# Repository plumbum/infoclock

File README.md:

HMI WiFi board
==============

Features
--------

  * STM32F103Cxxx MCU;
  * TFT LCD 3.2" with resistive touchscreen;
  * WiFi ESP8266 based module;
  * USB device;
  * MicroSD card slot;
  * Buzzer;
  * DHT22 themperature/humidity sensor.

Library
-------

  * [ChibiOS/RT](http://www.chibios.org/)
  * [uGFX](http://ugfx.org/)

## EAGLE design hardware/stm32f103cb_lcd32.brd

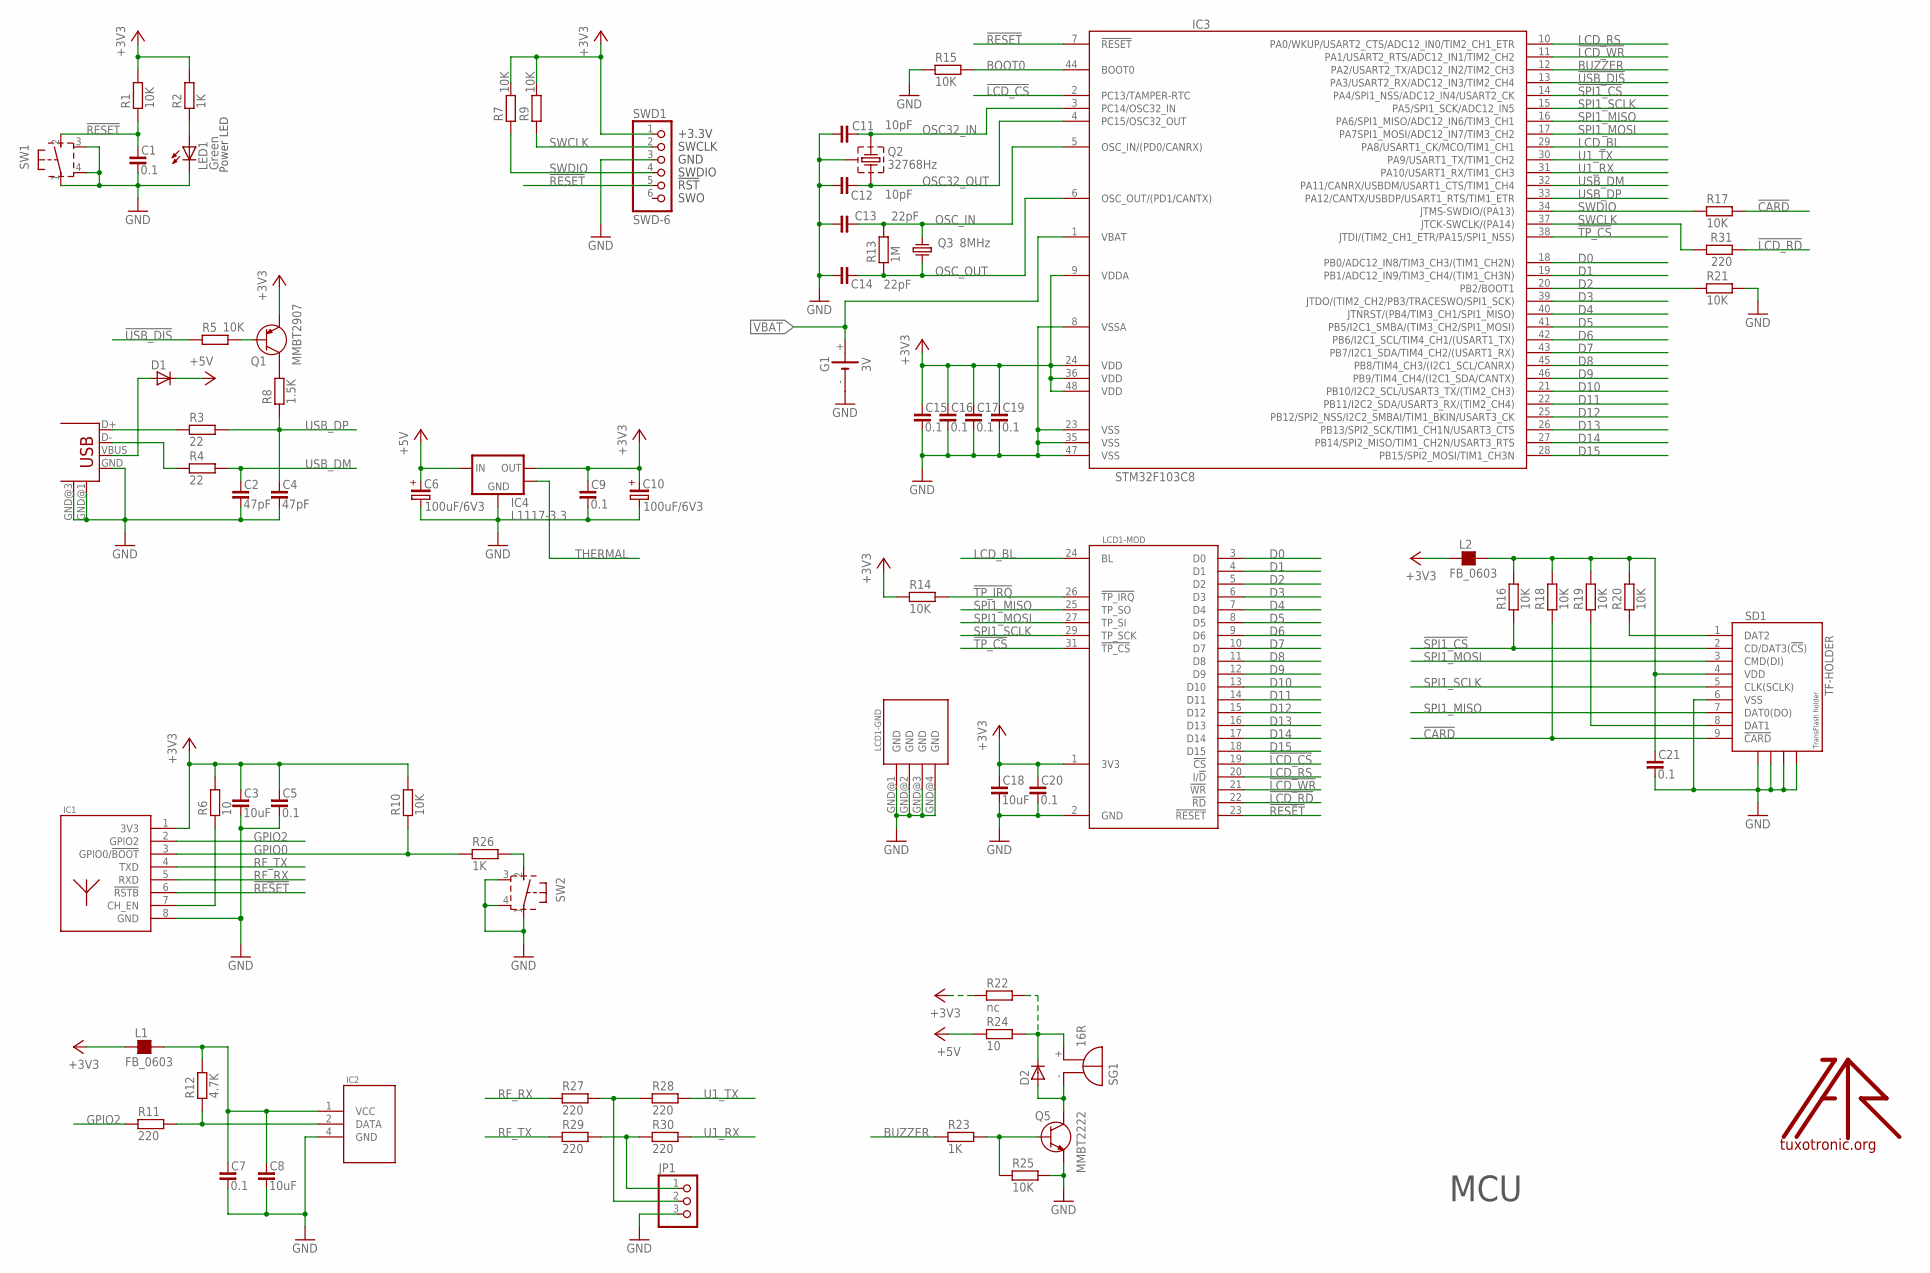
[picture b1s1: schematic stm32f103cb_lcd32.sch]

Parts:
C1, C5, C7, C15, C16, C17, C19, C20, C21: 0.1; C0603
C2, C4: 47pF; C0603
C3, C8, C18: 10uF; C0805
C6, C10: 100uF/6V3; SMC_D
C9: 0.1; C0805
C11, C12: 10pF; C0603
C13, C14: 22pF; C0603
D1: D-SMB; SMB
D2: D-SOD-80; SOD80
G1: 3V; SMT1220
IC1: ESP-11; ESP11
IC2: DHT22; DHT
IC3: STM32F103C8; LQFP48
IC4: L1117-3.3; SOT223-THP
JP1: PINHD-1X3_2.54S; 1X03SMALL
L1, L2: FB_0603; L0603
LCD1: YX32B
LED1: Green; CHIP-LED0805
LOGO1: LOGO; TT_LOGO
Q1: MMBT2907; SOT23
Q2: 32768Hz; TC38H-G
Q3: 8MHz; HC49/S
Q5: MMBT2222; SOT23
R1, R5, R7, R9, R10, R14, R15, R16, R17, R18, R19, R20, R21, R25: 10K; R0603
R2, R23, R26: 1K; R0603
R3, R4: 22; R0603
R6, R24: 10; R0603
R8: 1.5K; R0603
R11, R27, R28, R29, R30, R31: 220; R0603
R12: 4.7K; R0603
R13: 1M; R0603
R22: nc; R0603
SD1: TF-HOLDER; TF-PULL
SG1: 16R; F/QMBIII
SW1, SW2: 31-XX; B3F-31XX
SWD1: SWD-6; JTAG6PIN
USB1: USB-MB-S

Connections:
!CARD: R17.2, R18.1, SD1.9 (!CARD)
!LCD_CS: IC3.2 (PC13/TAMPER-RTC), LCD1.19 (!CS)
!LCD_RD: LCD1.22 (!RD), R31.1
!LCD_WR: IC3.11 (PA1/USART2_RTS/ADC12_IN1/TIM2_CH2), LCD1.21 (!WR)
!RESET: C1.1, IC1.6 (!RSTB), IC3.7 (!RESET), LCD1.23 (!RESET), R1.1, SW1.2 (S), SWD1.5
!SPI1_CS: IC3.14 (PA4/SPI1_NSS/ADC12_IN4/USART2_CK), R16.1, SD1.2 (CD/DAT3(!CS!))
!TP_CS: IC3.38 (JTDI/(TIM2_CH1_ETR/PA15/SPI1_NSS)), LCD1.31 (!TP_CS)
!TP_IRQ: LCD1.26 (!TP_IRQ), R14.2
!USB_DIS: IC3.13 (PA3/USART2_RX/ADC12_IN3/TIM2_CH4), R5.1
+3V3: C3.1, C5.1, C9.1, C10.+, C15.1, C16.1, C17.1, C18.1, C19.1, C20.1, IC1.1 (3V3), IC3.9 (VDDA), IC3.24 (VDD), IC3.36 (VDD), IC3.48 (VDD), IC4.2 (OUT), L1.1, L2.1, LCD1.1 (3V3), Q1.2 (E), R1.2, R2.2, R6.2, R7.2, R9.2, R10.2, R14.1, R22.1, SWD1.1
+5V: C6.+, D1.1 (C), IC4.3 (IN), R24.1
BOOT0: IC3.44 (BOOT0), R15.2
BUZZER: IC3.12 (PA2/USART2_TX/ADC12_IN2/TIM2_CH3), R23.1
D0: IC3.18 (PB0/ADC12_IN8/TIM3_CH3/(TIM1_CH2N)), LCD1.3 (D0)
D1: IC3.19 (PB1/ADC12_IN9/TIM3_CH4/(TIM1_CH3N)), LCD1.4 (D1)
D2: IC3.20 (PB2/BOOT1), LCD1.5 (D2), R21.1
D3: IC3.39 (JTDO/(TIM2_CH2/PB3/TRACESWO/SPI1_SCK)), LCD1.6 (D3)
D4: IC3.40 (JTNRST/(PB4/TIM3_CH1/SPI1_MISO)), LCD1.7 (D4)
D5: IC3.41 (PB5/I2C1_SMBA/(TIM3_CH2/SPI1_MOSI)), LCD1.8 (D5)
D6: IC3.42 (PB6/I2C1_SCL/TIM4_CH1/(USART1_TX)), LCD1.9 (D6)
D7: IC3.43 (PB7/I2C1_SDA/TIM4_CH2/(USART1_RX)), LCD1.10 (D7)
D8: IC3.45 (PB8/TIM4_CH3/(I2C1_SCL/CANRX)), LCD1.11 (D8)
D9: IC3.46 (PB9/TIM4_CH4/(I2C1_SDA/CANTX)), LCD1.12 (D9)
D10: IC3.21 (PB10/I2C2_SCL/USART3_TX/(TIM2_CH3)), LCD1.13 (D10)
D11: IC3.22 (PB11/I2C2_SDA/USART3_RX/(TIM2_CH4)), LCD1.14 (D11)
D12: IC3.25 (PB12/SPI2_NSS/I2C2_SMBAI/TIM1_BKIN/USAR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), LCD1.15 (D12)
D13: IC3.26 (PB13/SPI2_SCK/TIM1_CH1N/USART3_CTS), LCD1.16 (D13)
D14: IC3.27 (PB14/SPI2_MISO/TIM1_CH2N/USART3_RTS), LCD1.17 (D14)
D15: IC3.28 (PB15/SPI2_MOSI/TIM1_CH3N), LCD1.18 (D15)
GND: C1.2, C2.2, C3.2, C4.2, C5.2, C6.-, C7.2, C8.2, C9.2, C10.-, C11.2, C12.2, C13.2, C14.2, C15.2, C16.2, C17.2, C18.2, C19.2, C20.2, C21.2, G1.-, IC1.8 (GND), IC2.4 (GND), IC3.8 (VSSA), IC3.23 (VSS), IC3.35 (VSS), IC3.47 (VSS), IC4.1 (GND), JP1.3, LCD1.2 (GND), LCD1.GND@1 (GND), LCD1.GND@2 (GND), LCD1.GND@3 (GND), LCD1.GND@4 (GND), LED1.C, Q2.GND, Q5.2 (E), R15.1, R21.2, R25.2, SD1.6 (VSS), SD1.S1, SD1.S2, SD1.S3, SD1.S4, SW1.1, SW1.3 (GND1), SW1.4 (GND2), SW2.1, SW2.3 (GND1), SW2.4 (GND2), SWD1.3, USB1.GND, USB1.GND@1 (GND), USB1.GND@3 (GND)
GPIO0: IC1.3 (GPIO0/!BOOT), R10.1, R26.1
GPIO2: IC1.2 (GPIO2), R11.1
LCD_BL: IC3.29 (PA8/USART1_CK/MCO/TIM1_CH1), LCD1.24 (BL)
LCD_RS: IC3.10 (PA0/WKUP/USART2_CTS/ADC12_IN0/TIM2_CH1_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), LCD1.20 (I/!D)
unnamed: Q1.3 (C), R8.2
unnamed: D1.2 (A), USB1.VBUS
unnamed: LED1.A, R2.1
unnamed: Q5.1 (B), R23.2, R25.1
unnamed: IC1.7 (CH_EN), R6.1
unnamed: IC2.2 (DATA), R11.2, R12.1
unnamed: C21.1, L2.2, R16.2, R18.2, R19.2, R20.2, SD1.4 (VDD)
unnamed: R20.1, SD1.1 (DAT2)
unnamed: R19.1, SD1.8 (DAT1)
unnamed: R3.1, USB1.D+
unnamed: C7.1, C8.1, IC2.1 (VCC), L1.2, R12.2
unnamed: D2.2 (A), Q5.3 (C), SG1.- (+)
unnamed: D2.1 (C), R22.2, R24.2, SG1.+ (-)
unnamed: R26.2, SW2.2 (S)
unnamed: JP1.1, R29.2, R30.1
unnamed: JP1.2, R27.2, R28.1
unnamed: R4.1, USB1.D-
unnamed: Q1.1 (B), R5.2
OSC32_IN: C11.1, IC3.3 (PC14/OSC32_IN), Q2.2
OSC32_OUT: C12.1, IC3.4 (PC15/OSC32_OUT), Q2.1
OSC_IN: C13.1, IC3.5 (OSC_IN/(PD0/CANRX)), Q3.1, R13.2
OSC_OUT: C14.1, IC3.6 (OSC_OUT/(PD1/CANTX)), Q3.2, R13.1
RF_RX: IC1.5 (RXD), R27.1
RF_TX: IC1.4 (TXD), R29.1
SPI1_MISO: IC3.16 (PA6/SPI1_MISO/ADC12_IN6/TIM3_CH1), LCD1.25 (TP_SO), SD1.7 (DAT0(DO))
SPI1_MOSI: IC3.17 (PA7SPI1_MOSI/ADC12_IN7/TIM3_CH2), LCD1.27 (TP_SI), SD1.3 (CMD(DI))
SPI1_SCLK: IC3.15 (PA5/SPI1_SCK/ADC12_IN5), LCD1.29 (TP_SCK), SD1.5 (CLK(SCLK))
SWCLK: IC3.37 (JTCK-SWCLK/(PA14)), R9.1, R31.2, SWD1.2
SWDIO: IC3.34 (JTMS-SWDIO/(PA13)), R7.1, R17.1, SWD1.4
THERMAL: IC4.4 (MASS)
U1_RX: IC3.31 (PA10/USART1_RX/TIM1_CH3), R30.2
U1_TX: IC3.30 (PA9/USART1_TX/TIM1_CH2), R28.2
USB_DM: C2.1, IC3.32 (PA11/CANRX/USBDM/USART1_CTS/TIM1_CH4), R4.2
USB_DP: C4.1, IC3.33 (PA12/CANTX/USBDP/USART1_RTS/TIM1_ETR), R3.2, R8.1
VBAT: G1.+, IC3.1 (VBAT)

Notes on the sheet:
MCU
Power LED

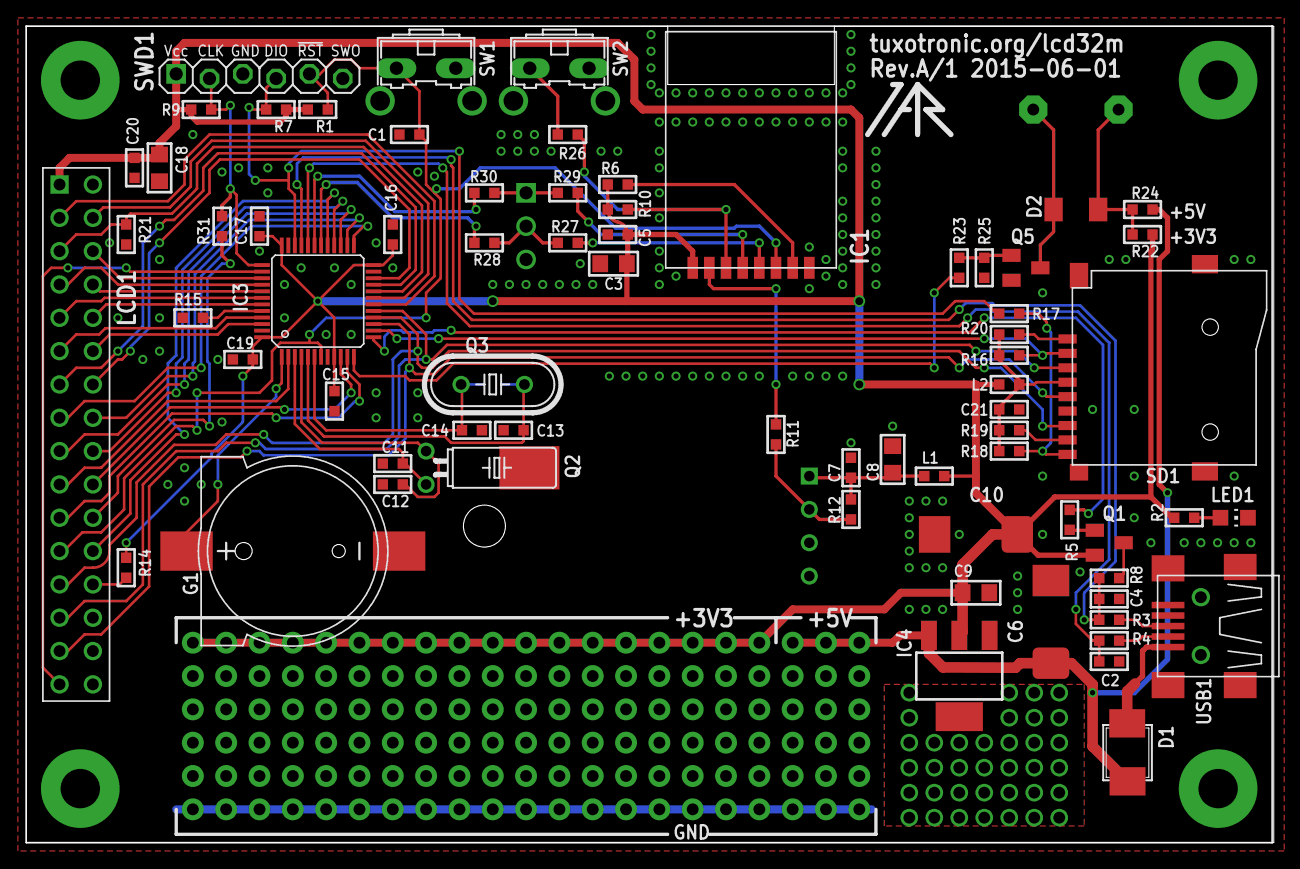
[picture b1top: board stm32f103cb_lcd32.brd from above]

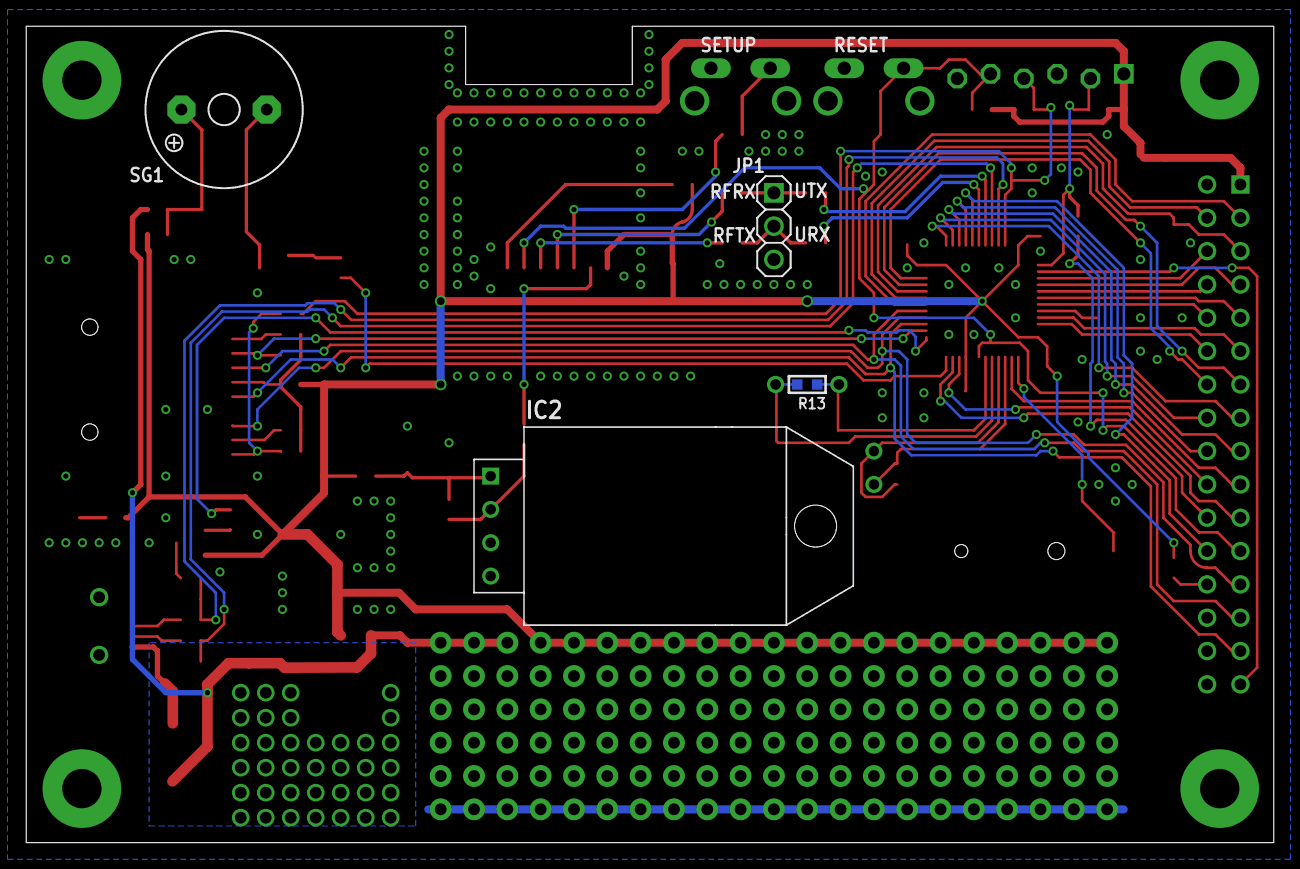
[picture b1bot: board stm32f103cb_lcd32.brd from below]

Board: 2 copper layers, 95.1 x 62.2 mm, 75 parts (4 on the bottom side), 68 nets.

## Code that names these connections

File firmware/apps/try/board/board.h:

/*
    ChibiOS/RT - Copyright (C) 2006-2013 Giovanni Di Sirio

    Licensed under the Apache License, Version 2.0 (the "License");
    you may not use this file except in compliance with the License.
    You may obtain a copy of the License at

        http://www.apache.org/licenses/LICENSE-2.0

    Unless required by applicable law or agreed to in writing, software
    distributed under the License is distributed on an "AS IS" BASIS,
    WITHOUT WARRANTIES OR CONDITIONS OF ANY KIND, either express or implied.
    See the License for the specific language governing permissions and
    limitations under the License.
*/

#ifndef _BOARD_H_
#define _BOARD_H_

/*
 * Setup for the Olimex STM33-H103 proto board.
 */

/*
 * Board identifier.
 */
#define BOARD_HMI_EASY
#define BOARD_NAME              "HMI easy controller"

/*
 * Board frequencies.
 */
#define STM32_LSECLK            32768
#define STM32_HSECLK            8000000

/*
 * MCU type, supported types are defined in ./os/hal/platforms/hal_lld.h.
 */
#define STM32F10X_MD

/*
 * IO pins assignments.
 */
#define GPIOC_LCD_CS            13
#define GPIOA_LCD_RS            0
#define GPIOA_LCD_WR            1
#define GPIOA_LCD_RD            2
#define GPIOA_USB_DISC          3
#define GPIOA_SPI1_CS           4
#define GPIOA_SPI1_SCLK         5
#define GPIOA_SPI1_MISO         6
#define GPIOA_SPI1_MOSI         7
#define GPIOA_LCD_BL            8
#define GPIOA_U1_TX             9
#define GPIOA_U1_RX             10
#define GPIOA_TP_CS             15

/*
 * I/O ports initial setup, this configuration is established soon after reset
 * in the initialization code.
 *
 * The digits have the following meaning:
 *   0 - Analog input.
 *   1 - Push Pull output 10MHz.
 *   2 - Push Pull output 2MHz.
 *   3 - Push Pull output 50MHz.
 *   4 - Digital input.
 *   5 - Open Drain output 10MHz.
 *   6 - Open Drain output 2MHz.
 *   7 - Open Drain output 50MHz.
 *   8 - Digital input with PullUp or PullDown resistor depending on ODR.
 *   9 - Alternate Push Pull output 10MHz.
 *   A - Alternate Push Pull output 2MHz.
 *   B - Alternate Push Pull output 50MHz.
 *   C - Reserved.
 *   D - Alternate Open Drain output 10MHz.
 *   E - Alternate Open Drain output 2MHz.
 *   F - Alternate Open Drain output 50MHz.
 * Please refer to the STM32 Reference Manual for details.
 */

/*
 * Port A setup.
 * Everything input with pull-up except:
 * PA0  - PP                (LCD_RS)
 * PA1  - PP                (#LCD_WR)
 * PA2  - PP                (#LCD_RD)
 * PA3  - PP                (#USB_DIS)
 * PA4  - PP                (#SPI1_CS)
 * PA5  - Alternate output  (SPI1_SCLK)
 * PA6  - Alternate input   (SPI1_MISO)
 * PA7  - Alternate output  (SPI1_MOSI)
 * PA8  - PP                (LCD_BL)
 * PA9  - Alternate output  (USART1 TX).
 * PA10 - Normal input      (USART1 RX).
 * PA15 - PP                (#TP_CS)
 */
#define VAL_GPIOACRL            0xB8B33333      /*  PA7...PA0 */
#define VAL_GPIOACRH            0x388888B3      /* PA15...PA8 */
#define VAL_GPIOAODR            0xFFFFFFFF

/*
 * Port B setup.
 * Everything input with pull-up except:
 * PB0-PB15 - PP (Display D0-D15)
 */
#define VAL_GPIOBCRL            0x88888888      /*  PB7...PB0 */
#define VAL_GPIOBCRH            0x88888888      /* PB15...PB8 */
#define VAL_GPIOBODR            0xFFFFFFFF

/*
 * Port C setup.
 * Everything input with pull-up except:
 * PC13 - Push Pull output (#LCD_CS).
 */
#define VAL_GPIOCCRL            0x88888888      /*  PC7...PC0 */
#define VAL_GPIOCCRH            0x88388888      /* PC15...PC8 */
#define VAL_GPIOCODR            0xFFFFFFFF

/*
 * Port D setup.
 * Everything input with pull-up except:
 * PD0  - Normal input (XTAL).
 * PD1  - Normal input (XTAL).
 */
#define VAL_GPIODCRL            0x88888844      /*  PD7...PD0 */
#define VAL_GPIODCRH            0x88888888      /* PD15...PD8 */
#define VAL_GPIODODR            0xFFFFFFFF

/*
 * Port E setup.
 * Everything input with pull-up except:
 */
#define VAL_GPIOECRL            0x88888888      /*  PE7...PE0 */
#define VAL_GPIOECRH            0x88888888      /* PE15...PE8 */
#define VAL_GPIOEODR            0xFFFFFFFF

/*
 * USB bus activation macro, required by the USB driver.
 */
#define usb_lld_connect_bus(usbp) palClearPad(GPIOA, GPIOA_USB_DISC)

/*
 * USB bus de-activation macro, required by the USB driver.
 */
#define usb_lld_disconnect_bus(usbp) palSetPad(GPIOA, GPIOA_USB_DISC)


#if !defined(_FROM_ASM_)
#ifdef __cplusplus
extern "C" {
#endif
  void boardInit(void);
#ifdef __cplusplus
}
#endif
#endif /* _FROM_ASM_ */

#endif /* _BOARD_H_ */

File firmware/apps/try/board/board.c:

/*
    ChibiOS/RT - Copyright (C) 2006-2013 Giovanni Di Sirio

    Licensed under the Apache License, Version 2.0 (the "License");
    you may not use this file except in compliance with the License.
    You may obtain a copy of the License at

        http://www.apache.org/licenses/LICENSE-2.0

    Unless required by applicable law or agreed to in writing, software
    distributed under the License is distributed on an "AS IS" BASIS,
    WITHOUT WARRANTIES OR CONDITIONS OF ANY KIND, either express or implied.
    See the License for the specific language governing permissions and
    limitations under the License.
*/

#include "ch.h"
#include "hal.h"

/**
 * @brief   PAL setup.
 * @details Digital I/O ports static configuration as defined in @p board.h.
 *          This variable is used by the HAL when initializing the PAL driver.
 */
#if HAL_USE_PAL || defined(__DOXYGEN__)
const PALConfig pal_default_config =
{
  {VAL_GPIOAODR, VAL_GPIOACRL, VAL_GPIOACRH},
  {VAL_GPIOBODR, VAL_GPIOBCRL, VAL_GPIOBCRH},
  {VAL_GPIOCODR, VAL_GPIOCCRL, VAL_GPIOCCRH},
  {VAL_GPIODODR, VAL_GPIODCRL, VAL_GPIODCRH},
  {VAL_GPIOEODR, VAL_GPIOECRL, VAL_GPIOECRH},
};
#endif

/*
 * Early initialization code.
 * This initialization must be performed just after stack setup and before
 * any other initialization.
 */
void __early_init(void) {

  stm32_clock_init();
}

/*
 * Board-specific initialization code.
 */
void boardInit(void) {
    AFIO->MAPR = AFIO->MAPR
        // | AFIO_MAPR_CAN_REMAP_REMAP2            /*!< CANRX mapped to PB8, CANTX mapped to PB9 */
        // | AFIO_MAPR_TIM3_REMAP_PARTIALREMAP     /*!< Partial remap (CH1/PB4, CH2/PB5, CH3/PB0, CH4/PB1) */
        // | AFIO_MAPR_USART3_REMAP_PARTIALREMAP  /* USART3 Partial remap TX/PC10, RX/PC11 */
        | AFIO_MAPR_SWJ_CFG_JTAGDISABLE         /* Disable JTAG, enable SWD */
    ;
}

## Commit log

2015-06-03 Control board (copy from https://bitbucket.org/plumbum/ttgui)
2015-06-03 Ignore eagle cad and vim files
2015-06-03 README
2015-06-03 Cutted ChibiOS 2.6.8
2015-06-03 Test board application
2015-06-03 chibios link, ugfx link
2015-06-03 Element values
2015-06-04 schematic & pcb in hardware directory
2015-06-04 project ignores
2015-06-04 Local vim configuration for syntastic
2015-06-04 ctags generator
2015-06-04 Move USB code to different file
2015-06-04 Local copy of chibios shell
2015-06-04 pin descriptions
2016-11-21 test serial port to esp-11
2017-08-08 board configuration fixes
2017-08-08 simple display access
2017-11-28 forth experiments
2017-12-05 try print fonts
2018-01-14 fixes
2018-10-08 schematic in pdf

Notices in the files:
parts and their libraries:
vreg-linear: 2009 Draw by Ivan A-R. License CC-BY-SA 3.0
